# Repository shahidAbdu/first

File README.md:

# first
<html>
hyujfftyrfaaaaaaaa
</html>

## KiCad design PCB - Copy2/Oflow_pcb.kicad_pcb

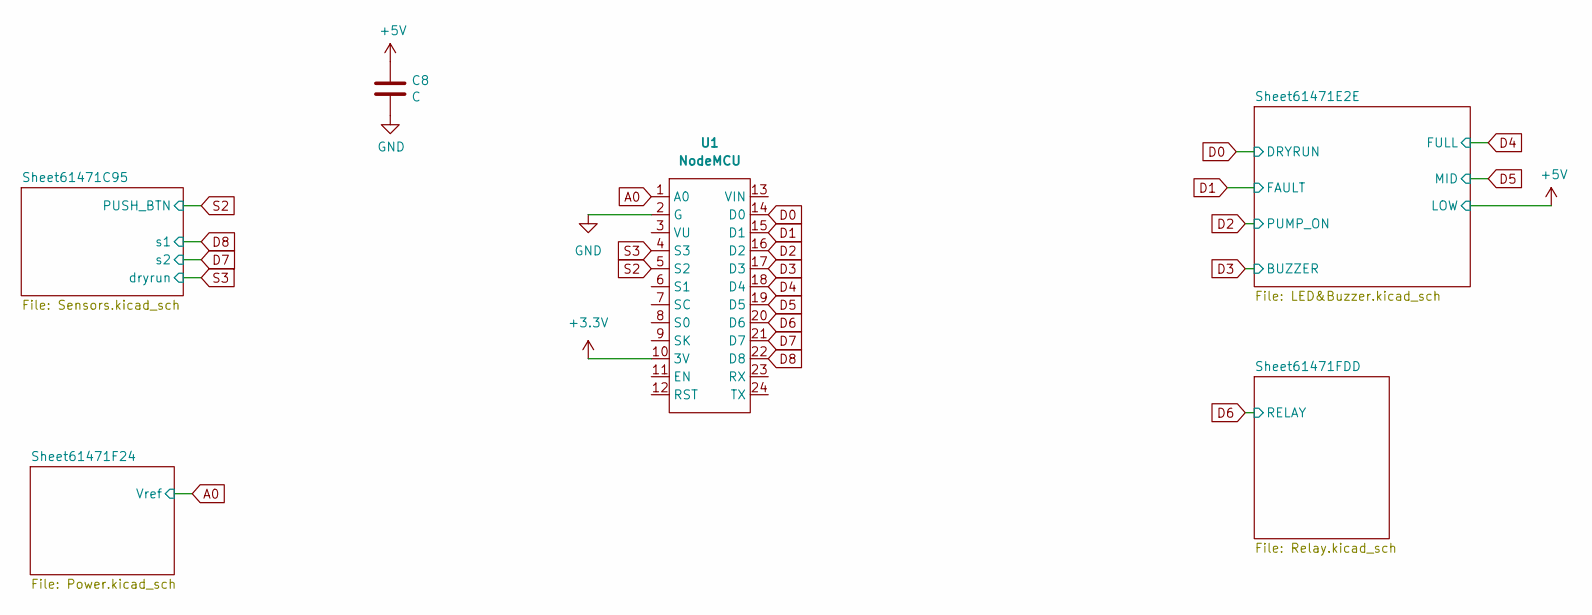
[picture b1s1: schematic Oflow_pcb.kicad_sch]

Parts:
C8: C; C_Disc_D4.7mm_W2.5mm_P5.00mm
U1: NodeMCU; NODE V1

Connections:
+3.3V: U1.10 (3V)
+5V: C8.1; also elsewhere on the board
A0: U1.1 (A0); also elsewhere on the board
D0: U1.14 (D0); also elsewhere on the board
D1: U1.15 (D1); also elsewhere on the board
D2: U1.16 (D2); also elsewhere on the board
D3: U1.17 (D3); also elsewhere on the board
D4: U1.18 (D4); also elsewhere on the board
D5: U1.19 (D5); also elsewhere on the board
D6: U1.20 (D6); also elsewhere on the board
D7: U1.21 (D7); also elsewhere on the board
D8: U1.22 (D8); also elsewhere on the board
GND: C8.2, U1.2 (G); also elsewhere on the board
S2: U1.5 (S2); also elsewhere on the board
S3: U1.4 (S3); also elsewhere on the board

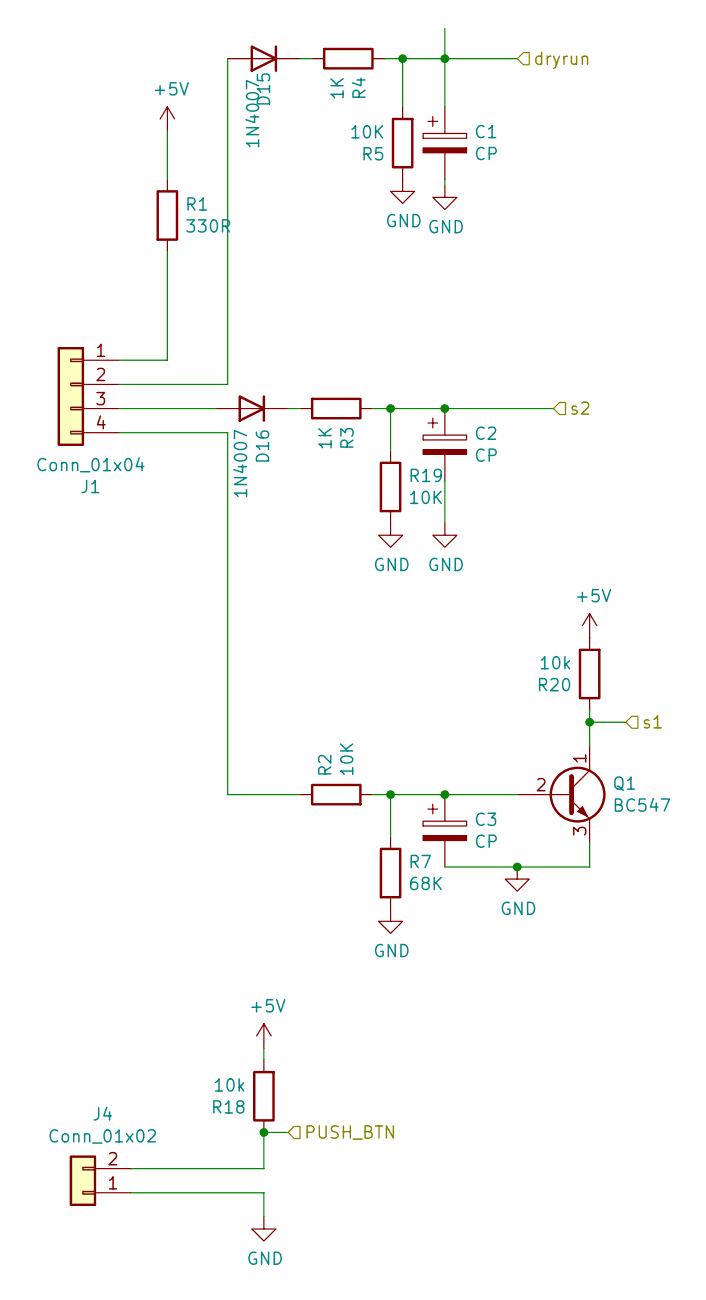
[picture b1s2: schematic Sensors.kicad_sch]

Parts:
C1, C2, C3: CP; CP_Radial_D5.0mm_P2.50mm
D15, D16: 1N4007; D_DO-41_SOD81_P10.16mm_Horizontal
J1: Conn_01x04; TerminalBlock_bornier-4_P5.08mm
J4: Conn_01x02; TerminalBlock_bornier-2_P5.08mm
Q1: BC547; TO-92L_Wide
R1: 330R; R_Axial_DIN0207_L6.3mm_D2.5mm_P10.16mm_Horizontal
R2, R5, R19: 10K; R_Axial_DIN0207_L6.3mm_D2.5mm_P10.16mm_Horizontal
R3, R4: 1K; R_Axial_DIN0207_L6.3mm_D2.5mm_P10.16mm_Horizontal
R7: 68K; R_Axial_DIN0207_L6.3mm_D2.5mm_P10.16mm_Horizontal
R18, R20: 10k; R_Axial_DIN0207_L6.3mm_D2.5mm_P10.16mm_Horizontal

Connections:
+5V: R1.1, R18.2, R20.2; also elsewhere on the board
D7: C2.1, R3.1, R19.1; also elsewhere on the board
D8: Q1.1 (C), R20.1; also elsewhere on the board
GND: C1.2, C2.2, C3.2, J4.1, Q1.3 (E), R5.1, R7.2, R19.2; also elsewhere on the board
unnamed: C3.1, Q1.2 (B), R2.2, R7.1
unnamed: D15.1 (K), R4.2
unnamed: D15.2 (A), J1.2
unnamed: D16.1 (K), R3.2
unnamed: D16.2 (A), J1.3
unnamed: J1.1, R1.2
unnamed: J1.4, R2.1
S2: J4.2, R18.1; also elsewhere on the board
S3: C1.1, R4.1, R5.2; also elsewhere on the board

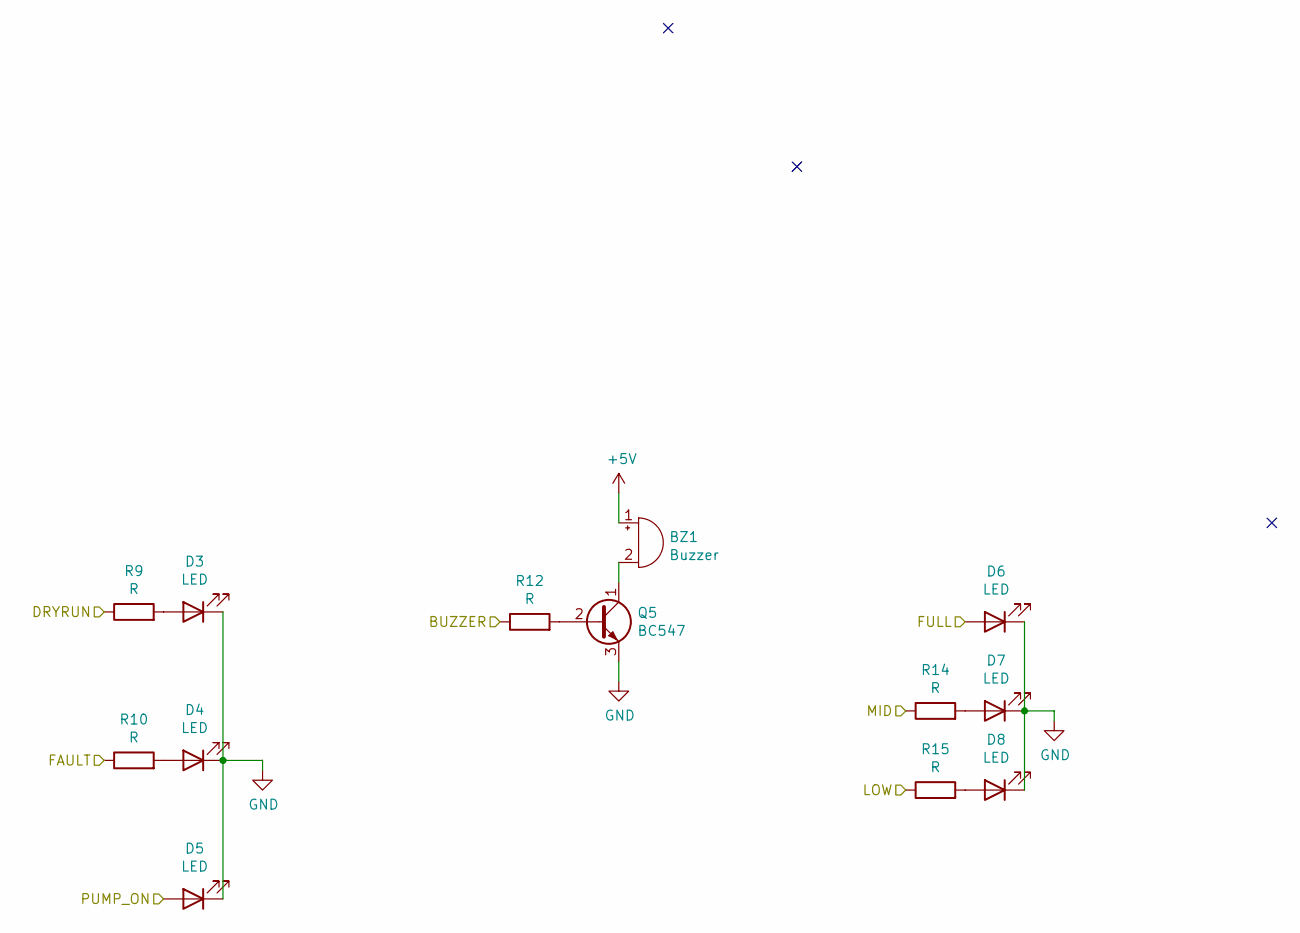
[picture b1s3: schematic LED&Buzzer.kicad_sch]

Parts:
BZ1: Buzzer; Buzzer_12x9.5RM7.6
D3, D4, D5, D6, D7, D8: LED; LED_D3.0mm
Q5: BC547; TO-92L_Wide
R9, R10, R12, R14, R15: R; R_Axial_DIN0207_L6.3mm_D2.5mm_P10.16mm_Horizontal

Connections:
+5V: BZ1.1 (-), R15.1; also elsewhere on the board
D0: R9.1; also elsewhere on the board
D1: R10.1; also elsewhere on the board
D2: D5.2 (A); also elsewhere on the board
D3: R12.1; also elsewhere on the board
D4: D6.2 (A); also elsewhere on the board
D5: R14.1; also elsewhere on the board
GND: D3.1 (K), D4.1 (K), D5.1 (K), D6.1 (K), D7.1 (K), D8.1 (K), Q5.3 (E); also elsewhere on the board
unnamed: BZ1.2 (+), Q5.1 (C)
unnamed: D3.2 (A), R9.2
unnamed: D4.2 (A), R10.2
unnamed: D7.2 (A), R14.2
unnamed: D8.2 (A), R15.2
unnamed: Q5.2 (B), R12.2

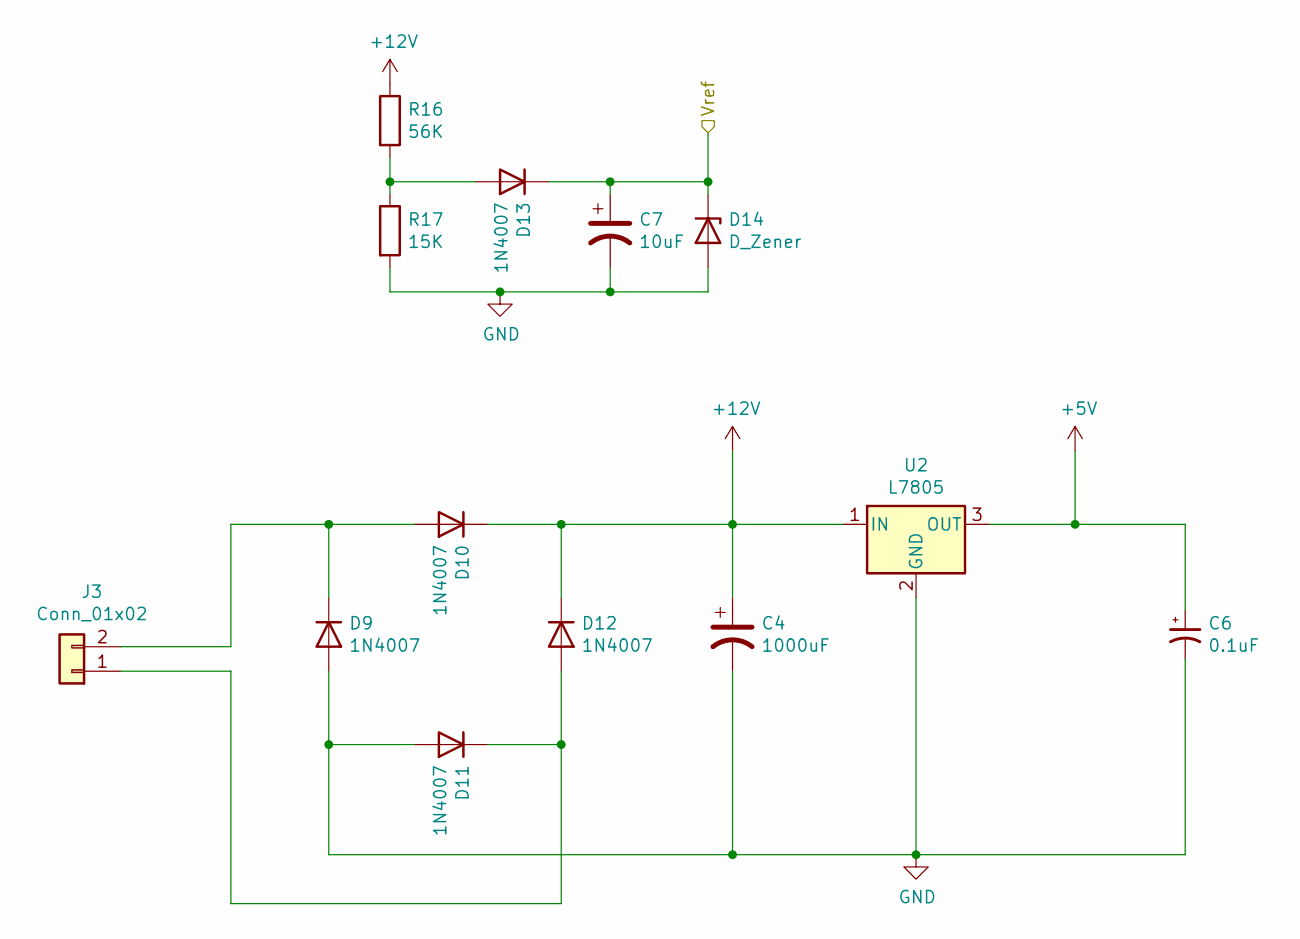
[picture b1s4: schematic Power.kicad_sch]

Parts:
C4: 1000uF; CP_Radial_D10.0mm_P5.00mm
C6: 0.1uF; CP_Radial_D5.0mm_P2.50mm
C7: 10uF; CP_Radial_D5.0mm_P2.50mm
D9, D10, D11, D12, D13: 1N4007; D_DO-41_SOD81_P10.16mm_Horizontal
D14: D_Zener; D_DO-41_SOD81_P10.16mm_Horizontal
J3: Conn_01x02; TerminalBlock_bornier-2_P5.08mm
R16: 56K; R_Axial_DIN0207_L6.3mm_D2.5mm_P10.16mm_Horizontal
R17: 15K; R_Axial_DIN0207_L6.3mm_D2.5mm_P10.16mm_Horizontal
U2: L7805; TO-220-3_Vertical

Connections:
+5V: C6.1, U2.3 (OUT); also elsewhere on the board
+12V: C4.1, D10.1 (K), D12.1 (K), R16.1, U2.1 (IN); also elsewhere on the board
A0: C7.1, D13.1 (K), D14.1 (K); also elsewhere on the board
GND: C4.2, C6.2, C7.2, D9.2 (A), D11.2 (A), D14.2 (A), R17.2, U2.2 (GND); also elsewhere on the board
unnamed: D9.1 (K), D10.2 (A), J3.2
unnamed: D11.1 (K), D12.2 (A), J3.1
unnamed: D13.2 (A), R16.2, R17.1

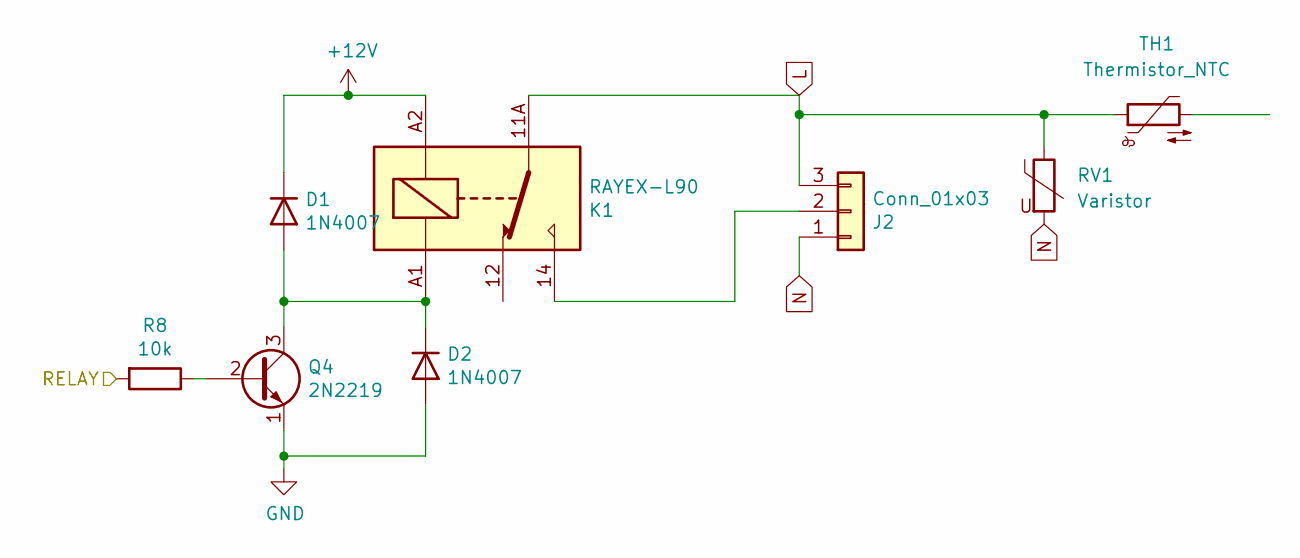
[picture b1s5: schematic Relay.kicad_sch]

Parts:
D1, D2: 1N4007; D_DO-41_SOD81_P10.16mm_Horizontal
J2: Conn_01x03; TerminalBlock_MetzConnect_Type175_RT02703HBLC_1x03_P7.50mm_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
K1: RAYEX-L90; Relay_SPDT_RAYEX-L90
Q4: 2N2219; TO-92L_Wide
R8: 10k; R_Axial_DIN0207_L6.3mm_D2.5mm_P10.16mm_Horizontal
RV1: Varistor; R_Axial_DIN0411_L9.9mm_D3.6mm_P20.32mm_Horizontal
TH1: Thermistor_NTC; R_Axial_DIN0411_L9.9mm_D3.6mm_P7.62mm_Vertical

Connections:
+12V: D1.1 (K), K1.A2; also elsewhere on the board
D6: R8.2; also elsewhere on the board
GND: D2.2 (A), Q4.1 (E); also elsewhere on the board
L: J2.3, K1.11A, K1.11B, RV1.1, TH1.1
N: J2.1, RV1.2
unnamed: D1.2 (A), D2.1 (K), K1.A1, Q4.3 (C)
unnamed: J2.2, K1.14
unnamed: Q4.2 (B), R8.1

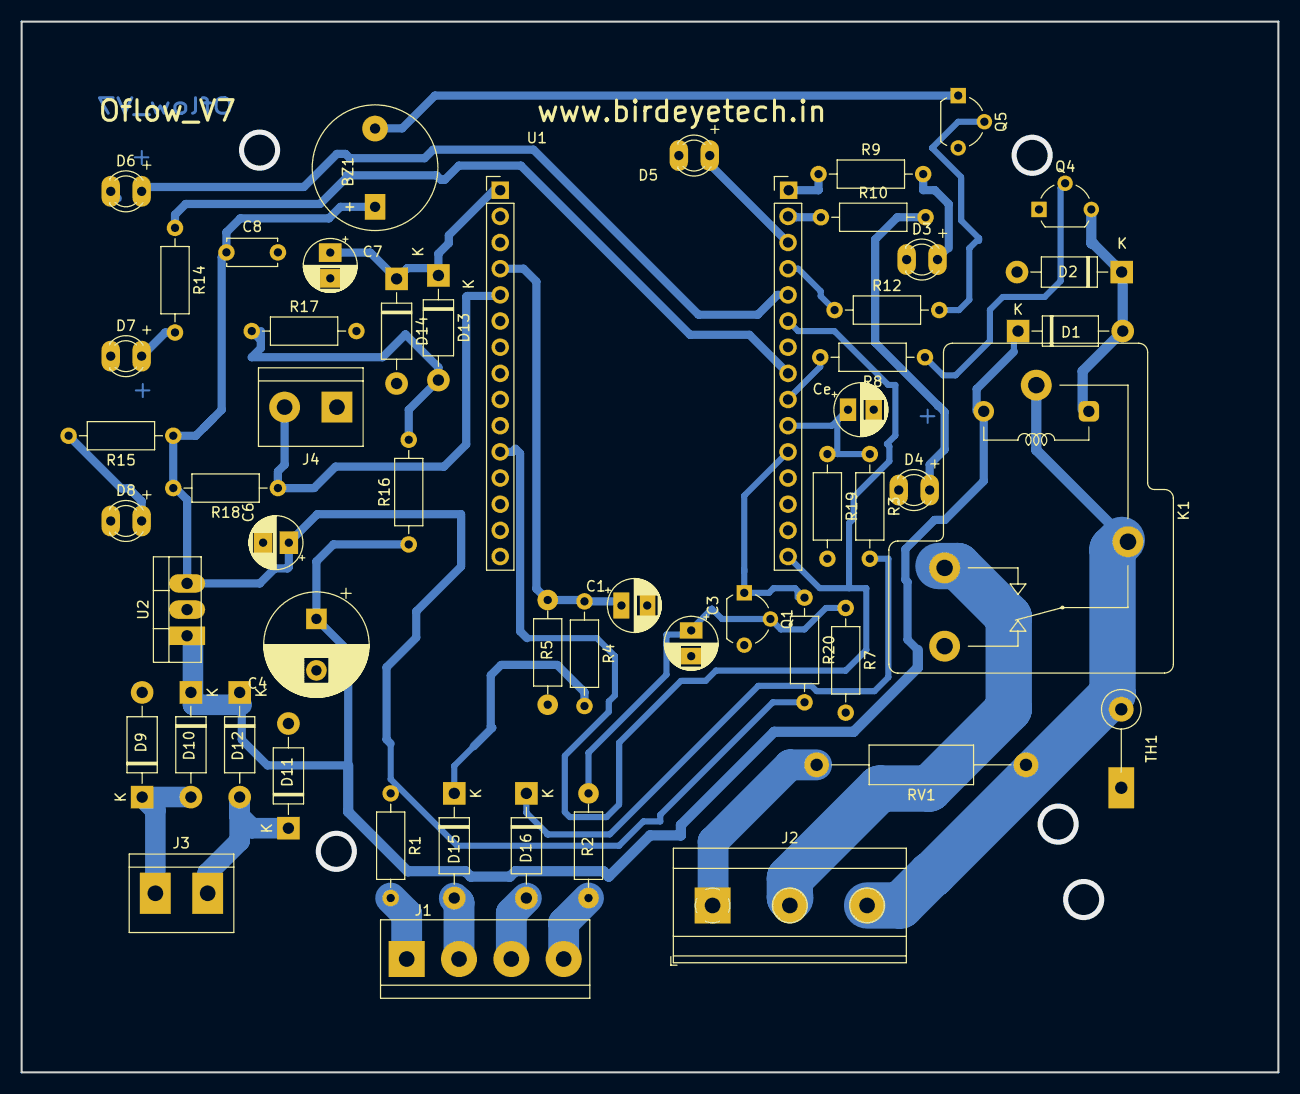
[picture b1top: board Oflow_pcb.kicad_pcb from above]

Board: 2 copper layers, 122.0 x 102.0 mm, 53 parts (0 on the bottom side), 36 nets.

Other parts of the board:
Ce: CP; CP_Radial_D5.0mm_P2.50mm

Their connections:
D7: Ce.1; also elsewhere on the board
GND: Ce.2; also elsewhere on the board

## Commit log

2023-04-11 Update README.md
    updated 2 feature
2023-04-11 Update README.md
    3 rd
2023-04-11 tohtml
2023-04-11 added v444
2023-04-11 added project
2023-04-11 ADDED VALUES
2023-04-13 added nod
2023-04-13 test
2023-04-13 test2
2023-04-13 foot print
2023-04-13 foot print changed
2023-04-17 nedd to connect ground
